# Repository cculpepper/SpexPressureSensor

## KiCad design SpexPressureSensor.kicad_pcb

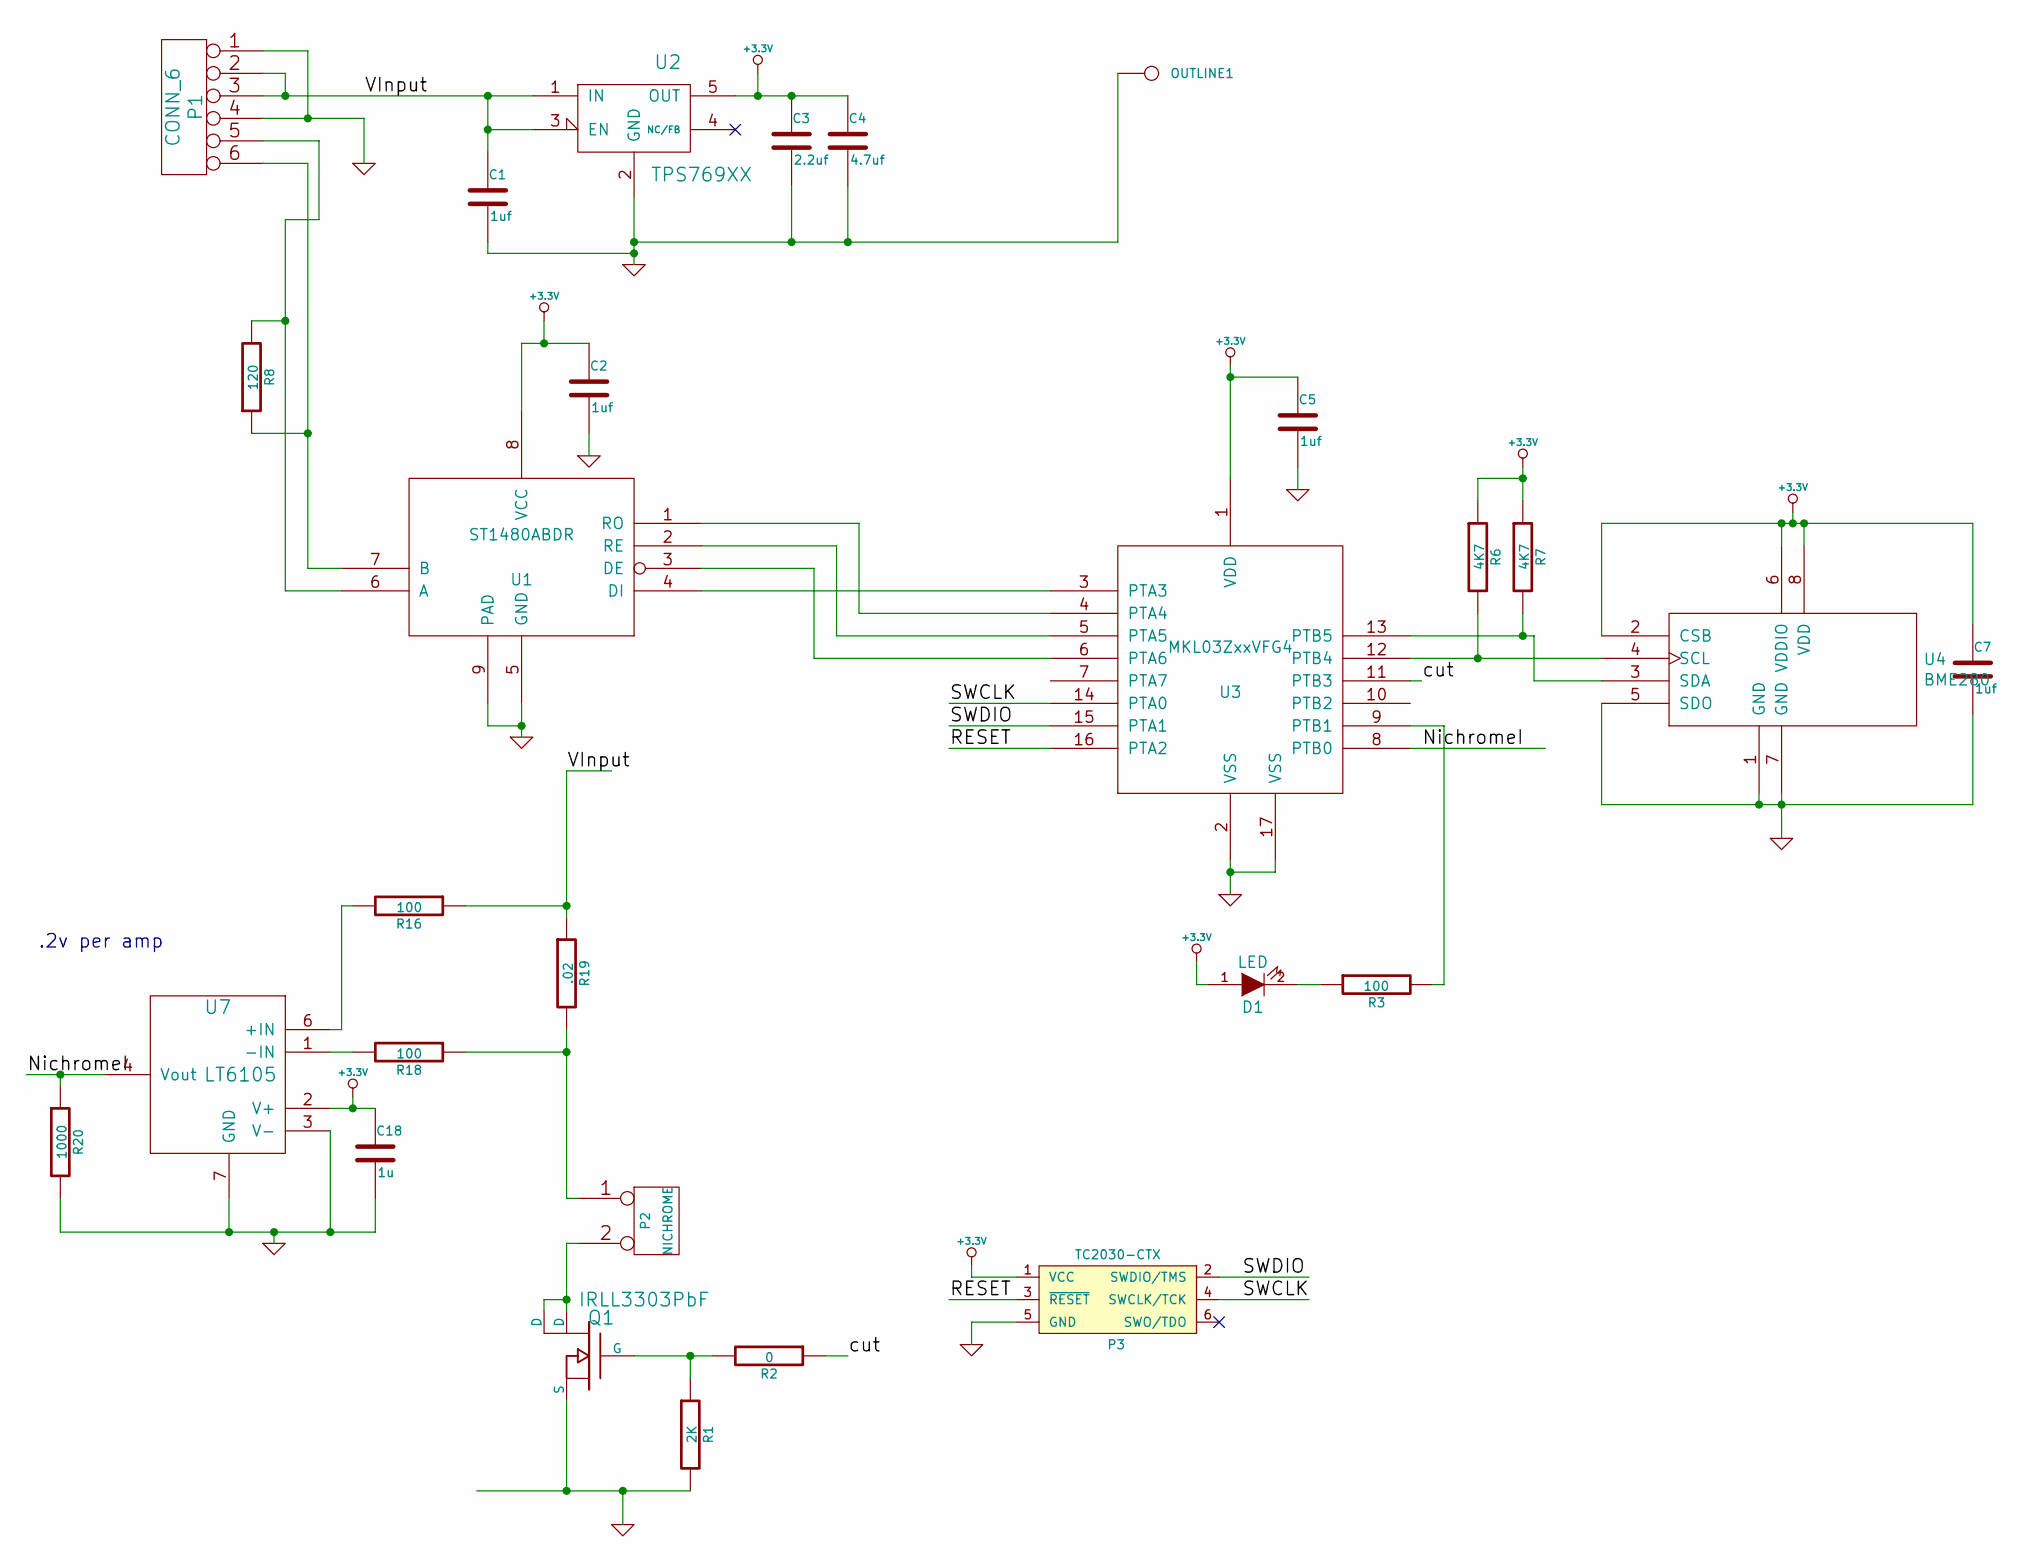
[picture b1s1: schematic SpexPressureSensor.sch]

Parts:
C1, C2, C5, C7: 1uf; C_0402
C3: 2.2uf; C_0603
C4: 4.7uf; C_0603
C18: 1u; C_0402
D1: LED; LED-0603
OUTLINE1: CONN_1; PLUG_OUTLINE
P1: CONN_6; Connector_Molex_PicoBlade_53047-0610
P2: NICHROME; Pin_Header_Straight_1x02
P3: TC2030-CTX; TC2030-NL_SMALL
Q1: IRLL3303PbF; SOT-223
R1: 2K; R_0402
R2: 0; R_0402
R3, R16, R18: 100; R_0402
R6, R7: 4K7; R_0402
R8: 120; R_0402
R19: .02; R_0805
R20: 1000; R_0402
U1: ST1480ABDR; DFN-8-1EP_3x3mm_Pitch0.5mm; Manufacturer PN LTC2851IDD
U2: TPS769XX; SOT-23-5; Manufacturer PN NCP500SN33T1G
U3: MKL03ZxxVFG4; QFN-16-1EP_3x3mm_Pitch0.5mm
U4: BME280; LGA-8
U7: LT6105

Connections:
+3.3V: C2.1, C3.1, C4.1, C5.1, C7.1, C18.1, D1.1 (A), P3.1 (VCC), R6.1, R7.1, U1.8 (VCC), U2.5 (OUT), U3.1 (VDD), U4.2 (CSB), U4.6 (VDDIO), U4.8 (VDD), U7.2 (V+)
/NichromeI: R20.1, U3.8 (PTB0), U7.4 (Vout)
/RESET: P3.3 (~RESET~), U3.16 (PTA2)
/SWCLK: P3.4 (SWCLK/TCK), U3.14 (PTA0)
/SWDIO: P3.2 (SWDIO/TMS), U3.15 (PTA1)
/VInput: C1.1, P1.2, P1.3, R16.1, R19.1, U2.1 (IN), U2.3 (EN)
/cut: R2.1, U3.11 (PTB3)
GND: C1.2, C2.2, C3.2, C4.2, C5.2, C7.2, C18.2, OUTLINE1.1, P1.1, P1.4, P3.5 (GND), Q1.3 (S), R1.2, R20.2, U1.5 (GND), U1.9 (PAD), U2.2 (GND), U3.2 (VSS), U3.17 (VSS), U4.1 (GND), U4.5 (SDO), U4.7 (GND), U7.3 (V-), U7.7 (GND)
unnamed: D1.2 (K), R3.1
unnamed: P1.5, R8.2, U1.6 (A)
unnamed: P1.6, R8.1, U1.7 (B)
unnamed: P2.1, R18.1, R19.2
unnamed: P2.2 (PM), Q1.2 (D), Q1.4 (D)
unnamed: Q1.1 (G), R1.1, R2.2
unnamed: R3.2, U3.9 (PTB1)
unnamed: R6.2, U3.12 (PTB4), U4.4 (SCL)
unnamed: R7.2, U3.13 (PTB5), U4.3 (SDA)
unnamed: R16.2, U7.6 (+IN)
unnamed: R18.2, U7.1 (-IN)
unnamed: U1.1 (RO), U3.4 (PTA4)
unnamed: U1.2 (RE), U3.5 (PTA5)
unnamed: U1.3 (DE), U3.6 (PTA6)
unnamed: U1.4 (DI), U3.3 (PTA3)

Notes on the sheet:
.2v per amp

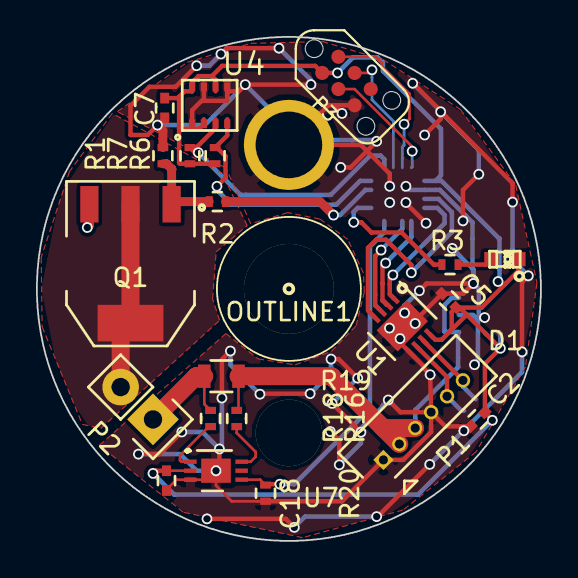
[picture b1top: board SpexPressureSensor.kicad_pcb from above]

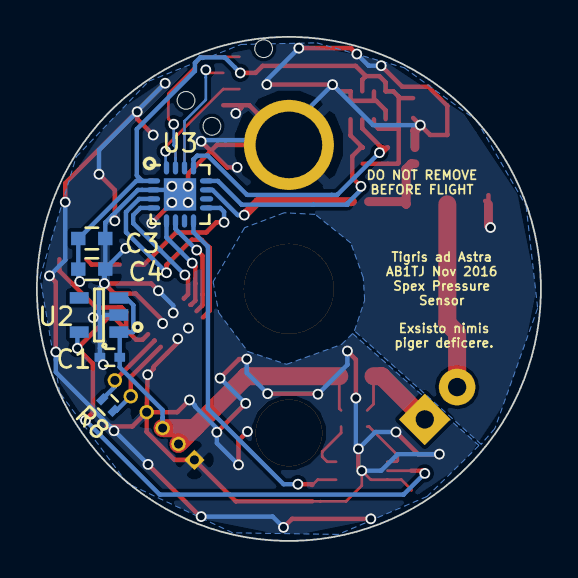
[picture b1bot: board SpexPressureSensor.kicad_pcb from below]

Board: 2 copper layers, 28.0 x 28.0 mm, 28 parts (6 on the bottom side), 23 nets.

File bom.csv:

Reference, Value, Footprint, Datasheet, Manufacturer PN
U3,MKL03ZxxVFG4,Housings_DFN_QFN:QFN-16-1EP_3x3mm_Pitch0.5mm,DOCUMENTATION
U1,ST1480ABDR,Housings_DFN_QFN:DFN-8-1EP_3x3mm_Pitch0.5mm,DOCUMENTATION,LTC2851IDD
U2,TPS769XX,Housings_SOT-23_SOT-143_TSOT-6:SOT-23-5,
C1,1uf,Capacitors_SMD:C_0402,
C3,2.2uf,Capacitors_SMD:C_0603,
C2,1uf,Capacitors_SMD:C_0402,
C7,1uf,Capacitors_SMD:C_0402,
R6,4K7,Resistors_SMD:R_0402,
R7,4K7,Resistors_SMD:R_0402,
C5,1uf,Capacitors_SMD:C_0402,
C4,4.7uf,Capacitors_SMD:C_0603,
R1,2K,Resistors_SMD:R_0402,
R2,0,Resistors_SMD:R_0402,
P2,NICHROME,Pin_Headers:Pin_Header_Straight_1x02,
R3,100,Resistors_SMD:R_0402,
D1,LED,LEDs:LED-0603,
Q1,IRLL3303PbF,SMD_Packages:SOT-223,
R8,120,Resistors_SMD:R_0402,
OUTLINE1,CONN_1,PlugOutline:PLUG_OUTLINE,
P3,TC2030-CTX,Tag-Connect:TC2030-NL_SMALL,
P1,CONN_6,Connectors_Molex:Connector_Molex_PicoBlade_53047-0610,
R19,.02,Resistors_SMD:R_0805,
R16,100,Resistors_SMD:R_0402,
R18,100,Resistors_SMD:R_0402,
U7,LT6105,LT6105:LT6105,
C18,1u,Capacitors_SMD:C_0402,
R20,1000,Resistors_SMD:R_0402,
U4,BME280,bme280:LGA-8,DOCUMENTATION

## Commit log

2015-11-18 Initial commit of the SpexPressureSensor hardware
    Has an accelerometer, barometer and thermometer
    Control is a KL03
    Has a big MOSFET to turn on nichrome wire
    Communicates using RS485.
2015-11-18 Made the hole for the wires an actual hole...
    Probably need to make it bigger.
2015-11-18 Moved some traces around.
2015-11-19 Added a current monitor on the nichrome.
2015-11-20 Realized the board was tooooo big.
2016-02-18 Finished board. Ready to go. Should add gerbers.
2016-02-18 Added a bom and gerbers.
2016-04-11 Changed the bmp180 for teh bme
2016-04-11 Commiting the rest of teh files
2016-04-12 Fixed some issues
